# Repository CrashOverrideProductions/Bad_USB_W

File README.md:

# BadUSB-W 

### Project: Arduino and ESP32 Based WiFi Capable Malicious USB 

<!-- Repo Cover Image -->

<!-- Repo Stats -->

## Details
The BadUSB is intended to be a budget alternative to the current offering of Keystroke Injection tools available on the market.

### What is a Keystroke Injection Attack?
A Keystroke Injection Attack Tool is a specially designed USB device, often disguised as a thumb drive, that automatically runs code on any host computer into which it is plugged. It does so by appearing to the computer as a USB HID ('Human Interface Device') keyboard and/or mouse, and then “typing” in keyboard shortcuts and commands.

This can be a vector for malicious code, and is potentially dangerous and destructive! This project aims to educate you and your “victim” on the dangers of these devices. Nothing is quite so memorable a lesson in security as plugging in an innocent looking device and being met with a flurry of terminal windows and text popping up, and receiving an automatically deployed desktop background that says “You just go PWND, be more careful next time!"

---
<!-- To Do List -->
## To Do List
- [X] Complete Readme.md
- [X] Build & Test Prototype
- [ ] Design Schematic
- [ ] Finalise Software
- [ ] Design Board
- [ ] Order Prototype PCBs
- [ ] Design 3D Print Shell
- [ ] Research Injection Moulded Shell

---
## Prototype Design

### BOM
```
| COMPONENT         | QTY | AUD$   |
|===================|=====|========|
| ESP32 DEVKIT V1   |  1  | $39.95 |
| ARDUINO LEONARDO  |  1  | $29.95 |
```

### Software
The software for this project is a modified version of the WiFi Duck firmware developed by [SpaceHunn](https://github.com/SpacehuhnTech/WiFiDuck "SpaceHunn") released under the MIT Licence.

### Hardware Configuration
```
| LEONARDO          | ESP32 DEVKIT V1 | SIGNAL NAME |
|===================|=================|=============|
| SCL               | GPIO-22         | I2C SCL     |
| SDA               | GPIO-21         | I2C SDA     |
| GND               | GND             | GND         |
```

<!-- Licencing Always at the Bottom -->
------------
### Licencing 

**Creative Commons: Attribution - NonCommercial - ShareAlike 4.0 International (CC BY-NC-SA 4.0)**

**You are free to:**

**Share** — copy and redistribute the material in any medium or format

**Adapt** — remix, transform, and build upon the material

**Under the following terms:**

**Attribution** — You must give appropriate credit, provide a link to the license, and indicate if changes were made. You may do so in any reasonable manner, but not in any way that suggests the licensor endorses you or your use.

**NonCommercial** — You may not use the material for commercial purposes.

**ShareAlike** — If you remix, transform, or build upon the material, you must distribute your contributions under the same license as the original.

No additional restrictions — You may not apply legal terms or technological measures that legally restrict others from doing anything the license permits.

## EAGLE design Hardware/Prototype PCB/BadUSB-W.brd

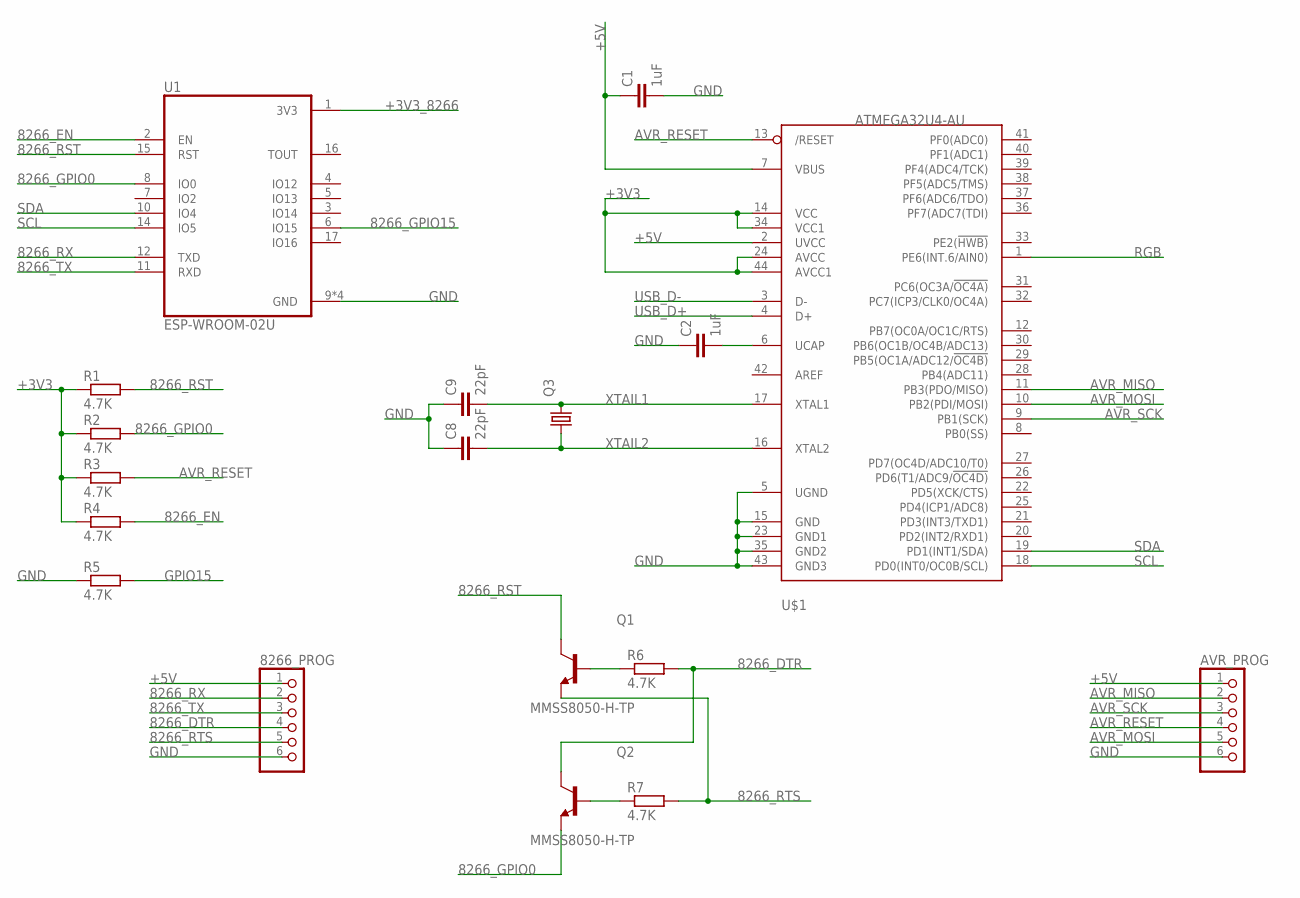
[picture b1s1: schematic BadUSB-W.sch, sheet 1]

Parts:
8266_PROG: PINHD-1X6; 1X06
AVR_PROG: PINHD-1X6; 1X06
C1, C2: 1uF; C0603K
C8, C9: 22pF; C0603K
Q1, Q2: MMSS8050-H-TP; TRANS_MMSS8050-H-TP
Q3: KX-7; 3.2X2.5_KX-7
R1, R2, R3, R4, R5, R6, R7: 4.7K; R0603
U1: ESP-WROOM-02U; MODULE_ESP-WROOM-02U
U$1: ATMEGA32U4-AU; TQFP44

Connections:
8266_DTR: 8266_PROG.4, Q2.3 (C), R6.2
8266_EN: R4.2, U1.2 (EN)
8266_GPIO0: Q2.2 (E), R2.2, U1.8 (IO0)
8266_GPIO15: U1.6 (IO15)
8266_RST: Q1.3 (C), R1.2, U1.15 (RST)
8266_RTS: 8266_PROG.5, Q1.2 (E), R7.2
8266_RX: 8266_PROG.2, U1.12 (TXD)
8266_TX: 8266_PROG.3, U1.11 (RXD)
+3V3: R1.1, R2.1, R3.1, R4.1, U$1.14 (VCC), U$1.24 (AVCC), U$1.34 (VCC1), U$1.44 (AVCC1); also elsewhere on the board
+3V3_8266: U1.1 (3V3)
+5V: 8266_PROG.1, AVR_PROG.1, C1.1, U$1.2 (UVCC), U$1.7 (VBUS); also elsewhere on the board
AVR_MISO: AVR_PROG.2, U$1.11 (PB3(PDO/MISO))
AVR_MOSI: AVR_PROG.5, U$1.10 (PB2(PDI/MOSI))
AVR_RESET: AVR_PROG.4, R3.2, U$1.13 (/RESET)
AVR_SCK: AVR_PROG.3, U$1.9 (PB1(SCK))
GND: 8266_PROG.6, AVR_PROG.6, C1.2, C2.1, C8.1, C9.1, R5.1, U1.9 (GND), U1.13 (GND), U1.18 (GND), U1.19 (GND), U$1.5 (UGND), U$1.15 (GND), U$1.23 (GND1), U$1.35 (GND2), U$1.43 (GND3); also elsewhere on the board
GPIO15: R5.2
unnamed: C2.2, U$1.6 (UCAP)
unnamed: Q1.1 (B), R6.1
unnamed: Q2.1 (B), R7.1
RGB: U$1.1 (PE6(INT.6/AIN0)); also elsewhere on the board
SCL: U1.14 (IO5), U$1.18 (PD0(INT0/OC0B/SCL))
SDA: U1.10 (IO4), U$1.19 (PD1(INT1/SDA))
USB_D+: U$1.4 (D+); also elsewhere on the board
USB_D-: U$1.3 (D-); also elsewhere on the board
XTAIL1: C9.2, Q3.3 (2), U$1.17 (XTAL1)
XTAIL2: C8.2, Q3.1, U$1.16 (XTAL2)

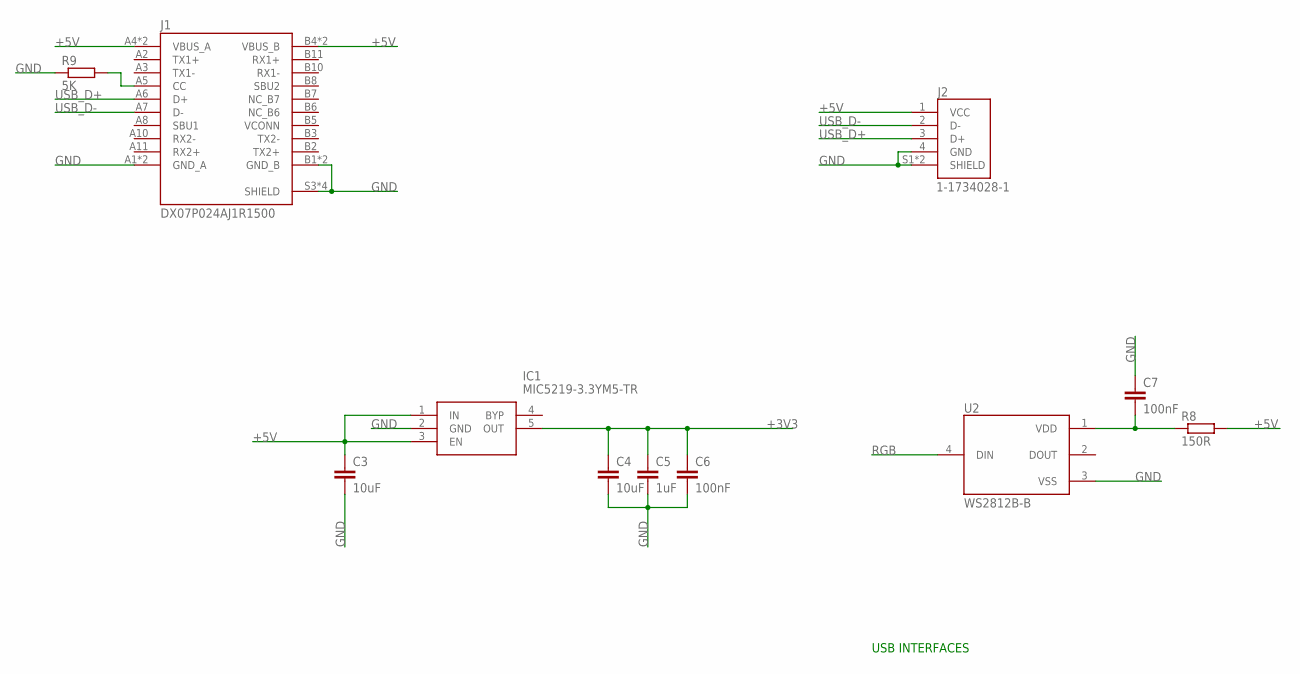
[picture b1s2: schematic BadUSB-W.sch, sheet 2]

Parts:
C3, C4: 10uF; C0603K
C5: 1uF; C0603K
C6, C7: 100nF; C0603K
IC1: MIC5219-3.3YM5-TR; SOT95P280X130-5N
J1: DX07P024AJ1R1500; JAE_DX07P024AJ1R1500
J2: 1-1734028-1; TE_1-1734028-1
R8: 150R; R0603
R9: 5K; R0603
U2: WS2812B-B; LED_WS2812B-B

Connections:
+3V3: C4.1, C5.1, C6.1, IC1.5 (OUT); also elsewhere on the board
+5V: C3.1, IC1.1 (IN), IC1.3 (EN), J1.A4 (VBUS_A), J1.A9 (VBUS_A), J1.B4 (VBUS_B), J1.B9 (VBUS_B), J2.1 (VCC), R8.2; also elsewhere on the board
GND: C3.2, C4.2, C5.2, C6.2, C7.1, IC1.2 (GND), J1.A1 (GND_A), J1.A12 (GND_A), J1.B1 (GND_B), J1.B12 (GND_B), J1.S3 (SHIELD), J1.S4 (SHIELD), J1.S5 (SHIELD), J1.S6 (SHIELD), J2.4 (GND), J2.S1 (SHIELD), J2.S2 (SHIELD), R9.1, U2.3 (VSS); also elsewhere on the board
unnamed: C7.2, R8.1, U2.1 (VDD)
unnamed: J1.A5 (CC), R9.2
RGB: U2.4 (DIN); also elsewhere on the board
USB_D+: J1.A6 (D+), J2.3 (D+); also elsewhere on the board
USB_D-: J1.A7 (D-), J2.2 (D-); also elsewhere on the board

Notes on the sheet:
USB INTERFACES

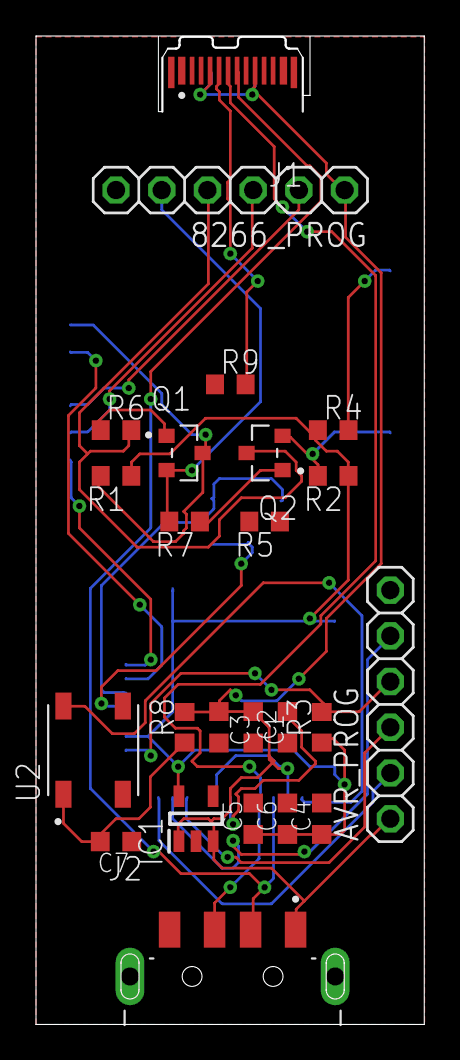
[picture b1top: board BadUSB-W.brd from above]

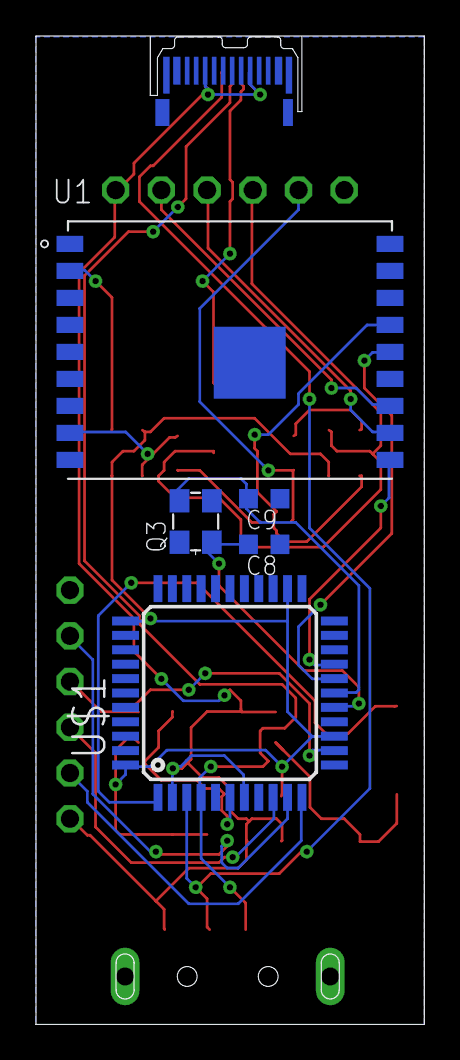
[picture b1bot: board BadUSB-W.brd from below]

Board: 2 copper layers, 21.6 x 54.9 mm, 29 parts (5 on the bottom side), 26 nets.

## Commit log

2021-07-02 Repo Upload
2021-07-02 img update
2021-07-02 testing
2021-07-02 resize
2021-07-08 SAMD21 Implementation

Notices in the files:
README.md:
License: CC-BY-NC-SA-4.0
parts and their libraries:
crystal-geyer_V1_0: Copyright: Geyer-Electronic
